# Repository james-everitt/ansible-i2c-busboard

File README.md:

# ansible-i2c-busboard

This is a remix of the monome I2C busboard for Teletype, but to mount on the back of ansible. Designed primarily for those wanting to experiment with the PolyES Ansible firmware and communicate with external I2C devices. Or its also handy if your Teletype is in and out of a case often and the Ansible is a bit more fixed

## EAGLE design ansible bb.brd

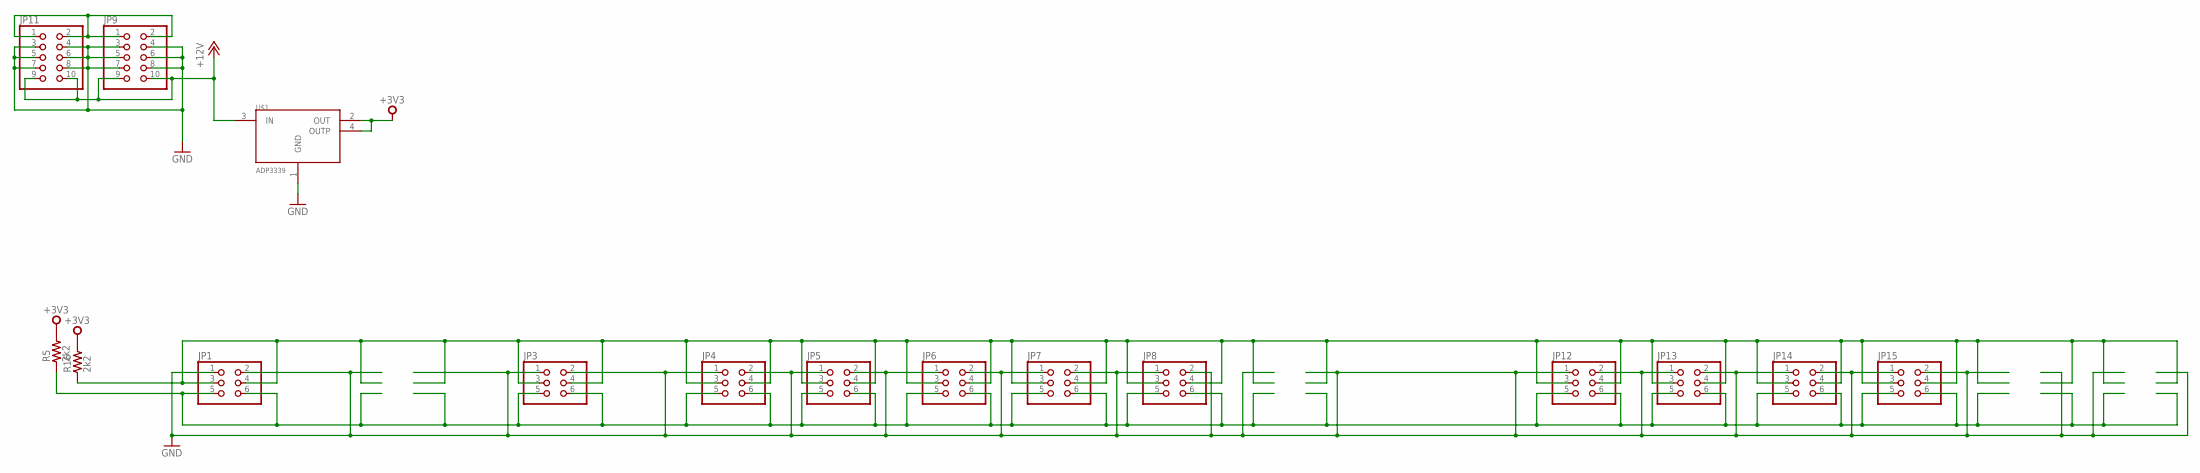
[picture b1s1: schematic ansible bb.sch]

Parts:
JP1, JP3, JP4, JP5, JP6, JP7, JP8, JP12, JP13, JP14, JP15: PINHD-2X3; 2X03
JP9, JP11: PINHD-2X5; 2X05
R5, R16: 2k2; R1206
U$1: ADP3339; SOT223

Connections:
+3V3: R5.2, R16.2, U$1.2 (OUT), U$1.4 (OUTP)
+12V: JP9.9, JP9.10, JP11.9, JP11.10, U$1.3 (IN)
GND: JP1.1, JP1.2, JP3.1, JP3.2, JP4.1, JP4.2, JP5.1, JP5.2, JP6.1, JP6.2, JP7.1, JP7.2, JP8.1, JP8.2, JP9.3, JP9.4, JP9.5, JP9.6, JP9.7, JP9.8, JP11.3, JP11.4, JP11.5, JP11.6, JP11.7, JP11.8, JP12.1, JP12.2, JP13.1, JP13.2, JP14.1, JP14.2, JP15.1, JP15.2, U$1.1 (GND)
unnamed: JP1.3, JP1.4, JP3.3, JP3.4, JP4.3, JP4.4, JP5.3, JP5.4, JP6.3, JP6.4, JP7.3, JP7.4, JP8.3, JP8.4, JP12.3, JP12.4, JP13.3, JP13.4, JP14.3, JP14.4, JP15.3, JP15.4, R16.1
unnamed: JP1.5, JP1.6, JP3.5, JP3.6, JP4.5, JP4.6, JP5.5, JP5.6, JP6.5, JP6.6, JP7.5, JP7.6, JP8.5, JP8.6, JP12.5, JP12.6, JP13.5, JP13.6, JP14.5, JP14.6, JP15.5, JP15.6, R5.1
unnamed: JP9.1, JP9.2, JP11.1, JP11.2

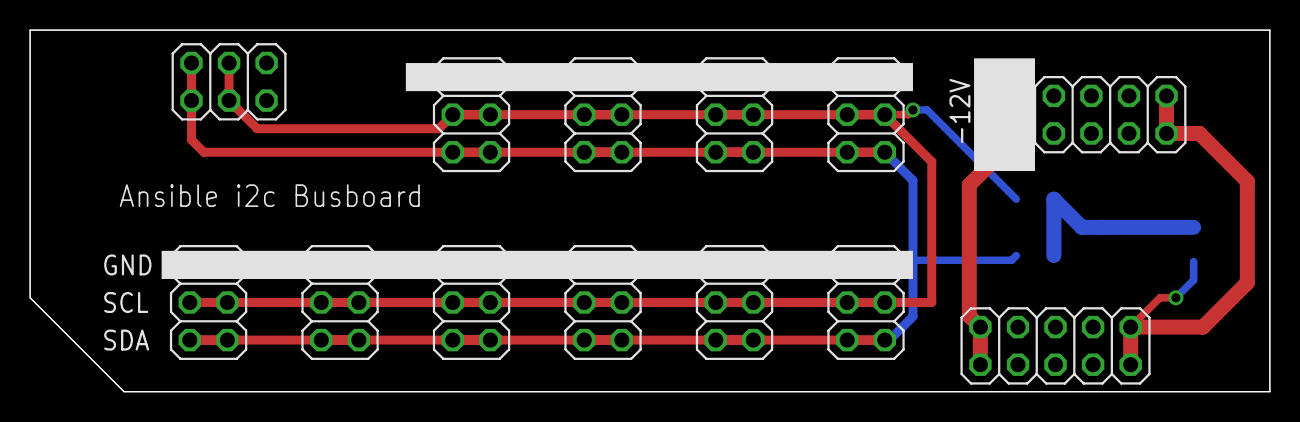
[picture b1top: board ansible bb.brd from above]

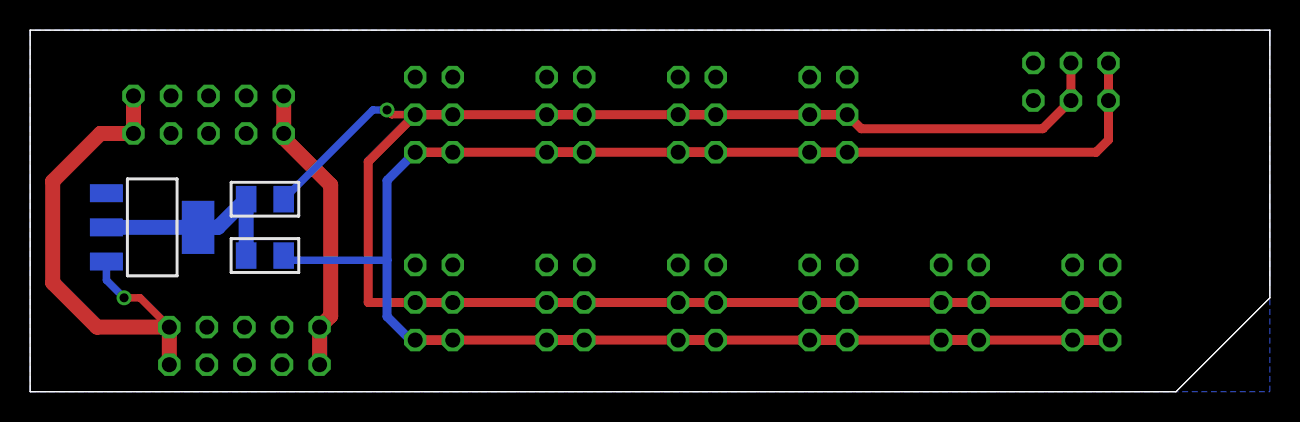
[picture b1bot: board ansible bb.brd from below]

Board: 2 copper layers, 83.8 x 24.4 mm, 16 parts (3 on the bottom side), 6 nets.

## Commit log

2018-11-15 Add files via upload
    Untested as of 15/11
